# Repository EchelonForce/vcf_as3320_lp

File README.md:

# Eurorack Low Pass VCF AS3320

This is a design for a eurorack low pass VCF using the AS3320 VCF chip.

Full writeup here: https://www.robotdialogs.com/2022/09/eurorack-vcf-module-low-pass-filter.html

This work is licensed under a Creative Commons Attribution-NonCommercial-ShareAlike 4.0 International License. https://creativecommons.org/licenses/by-nc-sa/4.0/

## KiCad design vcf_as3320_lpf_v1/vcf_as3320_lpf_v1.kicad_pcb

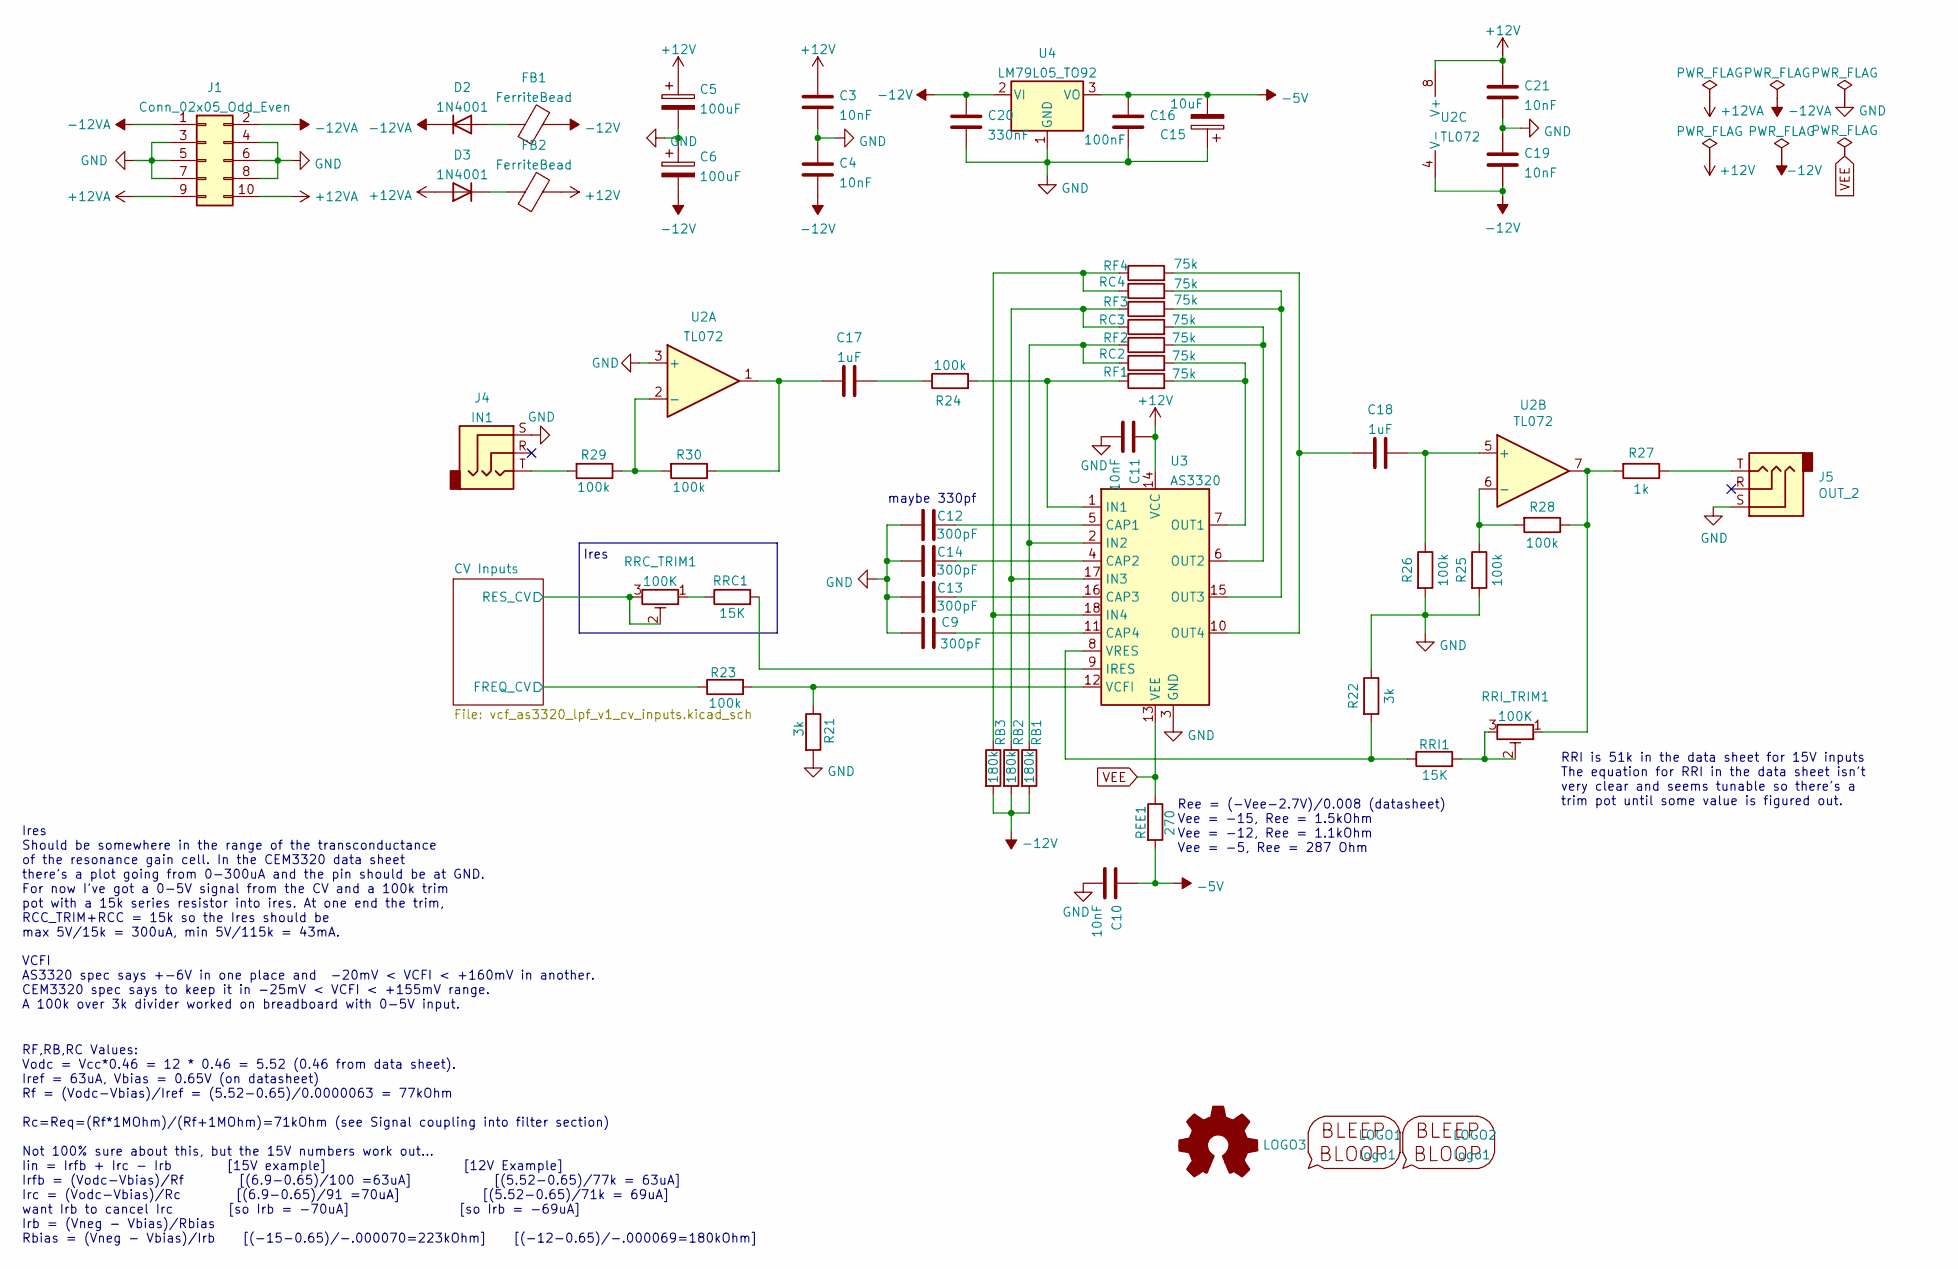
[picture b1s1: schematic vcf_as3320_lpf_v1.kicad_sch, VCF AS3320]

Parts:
C3, C4, C10, C11, C19, C21: 10nF; C_1206_3216Metric_Pad1.33x1.80mm_HandSolder
C5, C6: 100uF; CP_Radial_D5.0mm_P2.50mm
C9, C12, C13, C14: 300pF; C_1206_3216Metric_Pad1.33x1.80mm_HandSolder
C15: 10uF; CP_Radial_D5.0mm_P2.50mm
C16: 100nF; C_1206_3216Metric_Pad1.33x1.80mm_HandSolder
C17, C18: 1uF; C_1206_3216Metric_Pad1.33x1.80mm_HandSolder
C20: 330nF; C_1206_3216Metric_Pad1.33x1.80mm_HandSolder
D2, D3: 1N4001; D_A-405_P2.54mm_Vertical_KathodeUp
FB1, FB2: FerriteBead; L_Axial_L6.6mm_D2.7mm_P2.54mm_Vertical_Vishay_IM-2
J1: Conn_02x05_Odd_Even; IDC-Header_2x05_P2.54mm_Vertical
J4: IN1; Jack_3.5mm_MJ-355W_Vertical
J5: OUT_2; Jack_3.5mm_MJ-355W_Vertical
LOGO1: logo1; Logo1
LOGO2: logo1; Logo2
LOGO3: Logo_Open_Hardware_Small; OSHW-Symbol_6.7x6mm_SilkScreen
R21, R22: 3k; R_1206_3216Metric_Pad1.30x1.75mm_HandSolder
R23, R24, R25, R26, R28, R29, R30: 100k; R_1206_3216Metric_Pad1.30x1.75mm_HandSolder
R27: 1k; R_1206_3216Metric_Pad1.30x1.75mm_HandSolder
RB1, RB2, RB3: 180k; R_1206_3216Metric_Pad1.30x1.75mm_HandSolder
RC2, RC3, RC4: 75k; R_1206_3216Metric_Pad1.30x1.75mm_HandSolder
REE1: 270; R_1206_3216Metric_Pad1.30x1.75mm_HandSolder
RF1, RF2, RF3, RF4: 75k; R_1206_3216Metric_Pad1.30x1.75mm_HandSolder
RRC1: 15K; R_1206_3216Metric_Pad1.30x1.75mm_HandSolder
RRC_TRIM1: 100K; Potentiometer_Bourns_3296W_Vertical
RRI1: 15K; R_1206_3216Metric_Pad1.30x1.75mm_HandSolder
RRI_TRIM1: 100K; Potentiometer_Bourns_3296W_Vertical
U2: TL072; DIP-8_W7.62mm_Socket_LongPads
U3: AS3320; DIP-18_W7.62mm_Socket_LongPads
U4: LM79L05_TO92; TO-92_Inline_Wide

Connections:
+12V: C3.1, C5.1, C11.1, C21.1, FB2.2, U2.8 (V+), U3.14 (VCC); also elsewhere on the board
+12VA: D3.2 (A), J1.9, J1.10
-5V: C10.1, C15.2, C16.1, REE1.2, U4.3 (VO)
-12V: C4.2, C6.2, C19.2, C20.1, FB1.2, RB1.2, RB2.2, RB3.2, U2.4 (V-), U4.2 (VI); also elsewhere on the board
-12VA: D2.1 (K), J1.1, J1.2
/CV Inputs/FREQ_CV: R23.1; also elsewhere on the board
/CV Inputs/RES_CV: RRC_TRIM1.2, RRC_TRIM1.3; also elsewhere on the board
GND: C3.2, C4.1, C5.2, C6.1, C9.2, C10.2, C11.2, C12.2, C13.2, C14.2, C15.1, C16.2, C19.1, C20.2, C21.2, J1.3, J1.4, J1.5, J1.6, J1.7, J1.8, J4.S, J5.S, R21.2, R22.1, R25.2, R26.2, U2.3 (+), U3.3 (GND), U4.1 (GND); also elsewhere on the board
unnamed: C9.1, U3.11 (CAP4)
unnamed: C12.1, U3.5 (CAP1)
unnamed: C13.1, U3.16 (CAP3)
unnamed: C14.1, U3.4 (CAP2)
unnamed: C17.1, R24.1
unnamed: C17.2, R30.1, U2.1
unnamed: C18.1, R26.1, U2.5 (+)
unnamed: C18.2, RF4.2, U3.10 (OUT4)
unnamed: D2.2 (A), FB1.1
unnamed: D3.1 (K), FB2.1
unnamed: J4.T, R29.2
unnamed: J5.T, R27.1
unnamed: R22.2, RRI1.1, U3.8 (VRES)
unnamed: R21.1, R23.2, U3.12 (VCFI)
unnamed: R24.2, RF1.1, U3.1 (IN1)
unnamed: R27.2, R28.1, RRI_TRIM1.1, U2.7
unnamed: R25.1, R28.2, U2.6 (-)
unnamed: R29.1, R30.2, U2.2 (-)
unnamed: RB1.1, RC2.1, RF2.1, U3.2 (IN2)
unnamed: RB2.1, RC3.1, RF3.1, U3.17 (IN3)
unnamed: RB3.1, RC4.1, RF4.1, U3.18 (IN4)
unnamed: RC2.2, RF1.2, U3.7 (OUT1)
unnamed: RC3.2, RF2.2, U3.6 (OUT2)
unnamed: RC4.2, RF3.2, U3.15 (OUT3)
unnamed: RRC1.1, RRC_TRIM1.1
unnamed: RRC1.2, U3.9 (IRES)
unnamed: RRI1.2, RRI_TRIM1.2, RRI_TRIM1.3
VEE: REE1.1, U3.13 (VEE)

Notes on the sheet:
maybe 330pf
VCFI AS3320 spec says +-6V in one place and -20mV < VCFI < +160mV in another. CEM3320 spec says to keep it in -25mV < VCFI < +155mV range. A 100k over 3k divider worked on breadboard with 0-5V input.
RRI is 51k in the data sheet for 15V inputs The equation for RRI in the data sheet isn't very clear and seems tunable so there's a trim pot until some value is figured out.
RF,RB,RC Values: Vodc = Vcc*0.46 = 12 * 0.46 = 5.52 (0.46 from data sheet). Iref = 63uA, Vbias = 0.65V (on datasheet) Rf = (Vodc-Vbias)/Iref = (5.52-0.65)/0.0000063 = 77kOhm Rc=Req=(Rf*1MOhm)/(Rf+1MOhm)=71kOhm (see Signal coupling into filter section) Not 100% sure about this, but the 15V numbers w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
Ires Should be somewhere in the range of the transconductance of the resonance gain cell. In the CEM3320 data sheet there's a plot going from 0-300uA and the pin should be at GND. For now I've got a 0-5V signal from the CV and a 100k trim pot with a 15k series resistor into ires. At one end the tri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
Ires
Ree = (-Vee-2.7V)/0.008 (datasheet) Vee = -15, Ree = 1.5kOhm Vee = -12, Ree = 1.1kOhm Vee = -5, Ree = 287 Ohm

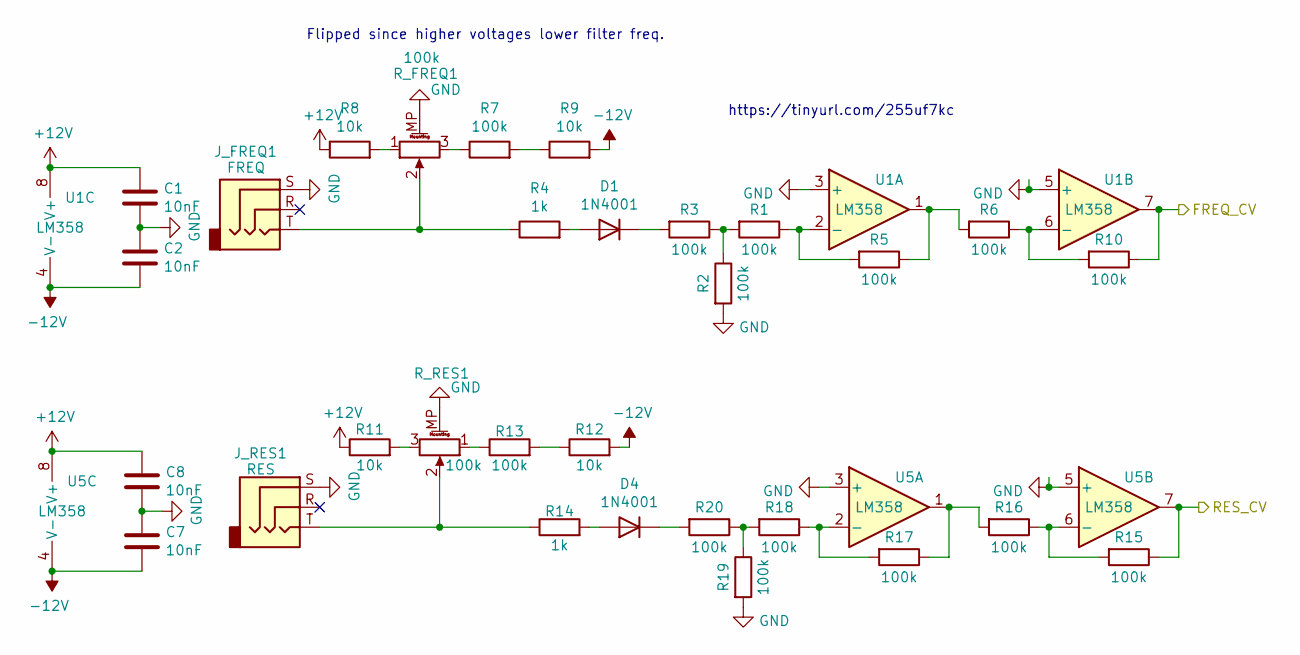
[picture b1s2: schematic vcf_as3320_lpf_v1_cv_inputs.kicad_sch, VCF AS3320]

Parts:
C1, C2, C7, C8: 10nF; C_1206_3216Metric_Pad1.33x1.80mm_HandSolder
D1, D4: 1N4001; D_A-405_P2.54mm_Vertical_KathodeUp
J_FREQ1: FREQ; Jack_3.5mm_MJ-355W_Vertical
J_RES1: RES; Jack_3.5mm_MJ-355W_Vertical
R1, R2, R3, R5, R6, R7, R10, R13, R15, R16, R17, R18, R19, R20: 100k; R_1206_3216Metric_Pad1.30x1.75mm_HandSolder
R4, R14: 1k; R_1206_3216Metric_Pad1.30x1.75mm_HandSolder
R8, R9, R11, R12: 10k; R_1206_3216Metric_Pad1.30x1.75mm_HandSolder
R_FREQ1: 100k; Potentiometer_Alpha_RD901F-40-00D_Single_Vertical_w_3d
R_RES1: 100k; Potentiometer_Alpha_RD901F-40-00D_Single_Vertical_w_3d
U1, U5: LM358; DIP-8_W7.62mm_Socket_LongPads

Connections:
+12V: C1.2, C8.2, R8.1, R11.1, U1.8 (V+), U5.8 (V+); also elsewhere on the board
-12V: C2.1, C7.1, R9.2, R12.2, U1.4 (V-), U5.4 (V-); also elsewhere on the board
/CV Inputs/FREQ_CV: R10.1, U1.7; also elsewhere on the board
/CV Inputs/RES_CV: R15.1, U5.7; also elsewhere on the board
GND: C1.1, C2.2, C7.2, C8.1, J_FREQ1.S, J_RES1.S, R2.2, R19.2, R_FREQ1.MP (MountPin), R_RES1.MP (MountPin), U1.3 (+), U1.5 (+), U5.3 (+), U5.5 (+); also elsewhere on the board
unnamed: D1.1 (K), R3.2
unnamed: D1.2 (A), R4.2
unnamed: D4.1 (K), R20.2
unnamed: D4.2 (A), R14.2
unnamed: J_FREQ1.T, R4.1, R_FREQ1.2
unnamed: J_RES1.T, R14.1, R_RES1.2
unnamed: R1.1, R5.2, U1.2 (-)
unnamed: R1.2, R2.1, R3.1
unnamed: R6.1, R10.2, U1.6 (-)
unnamed: R5.1, R6.2, U1.1
unnamed: R7.1, R_FREQ1.3
unnamed: R7.2, R9.1
unnamed: R8.2, R_FREQ1.1
unnamed: R11.2, R_RES1.3
unnamed: R13.1, R_RES1.1
unnamed: R12.1, R13.2
unnamed: R15.2, R16.1, U5.6 (-)
unnamed: R16.2, R17.1, U5.1
unnamed: R17.2, R18.1, U5.2 (-)
unnamed: R18.2, R19.1, R20.1

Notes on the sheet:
https://tinyurl.com/255uf7kc
Flipped since higher voltages lower filter freq.

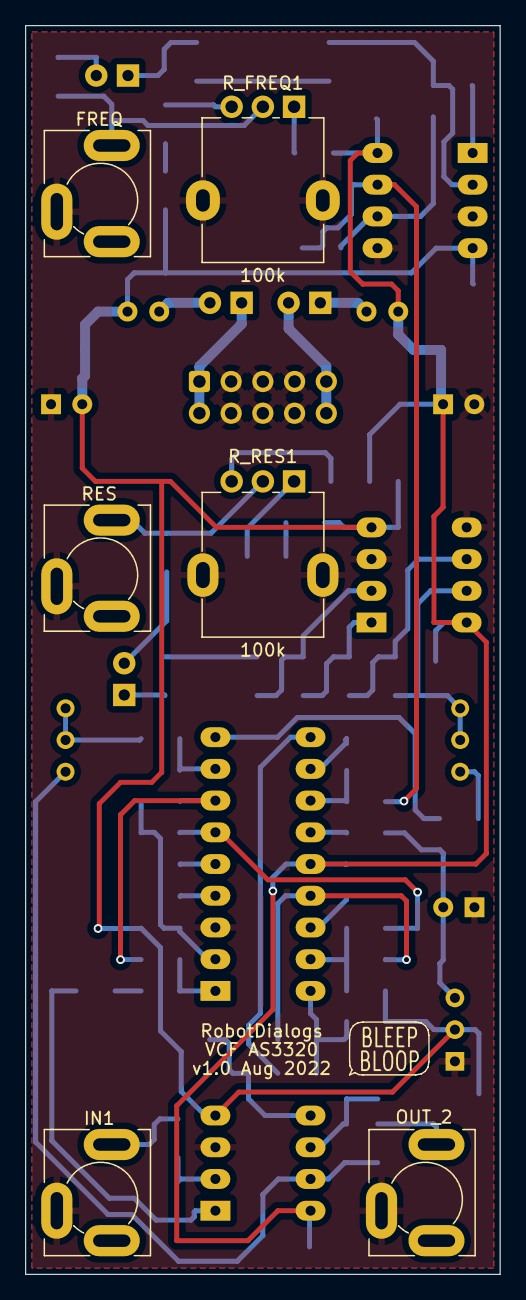
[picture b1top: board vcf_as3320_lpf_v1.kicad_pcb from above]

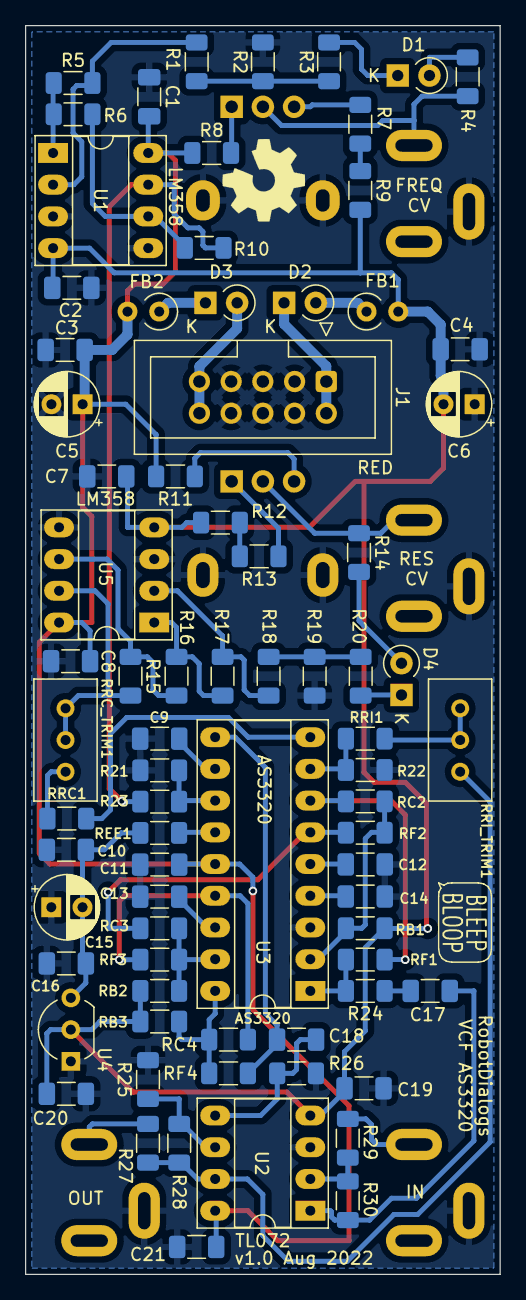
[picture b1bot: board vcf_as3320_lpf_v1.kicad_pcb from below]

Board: 2 copper layers, 38.0 x 100.0 mm, 87 parts (79 on the bottom side), 56 nets.

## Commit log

2022-08-04 Initial commit with .gitignore
2022-08-04 Schematic draft done and breadboard verified
2022-08-06 Draft layout done no routing
2022-08-06 Draft routing done
2022-08-10 Geographic rename, silkscreen cleanup
2022-09-10 panelized outputs and notes
2022-09-10 Front Panel design files
2022-09-10 Add readme and pdfs
